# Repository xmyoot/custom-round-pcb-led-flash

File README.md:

# Round LED Flash — Annular Ring Camera Strobe

An advanced, hardware-interlocked **annular ring LED camera flash and video light** engineered in **KiCad 10.0.7**. Designed to fit concentric around photographic lens barrels (84.0 mm OD × 55.0 mm ID), the board integrates a **supercapacitor-buffered boost powertrain**, dual regulated current sinks for a tunable white COB, hardware-enforced timing and safety interlocks, and Bluetooth Low Energy (BLE 5.0) control via an **ESP32-C3**.

---

## 1. System Architecture & Powertrain

```mermaid
flowchart TD
    subgraph PowerInput [Power & Battery Management]
        USB["USB Type-C Receptacle (J1)<br/>GCT USB4085"] --> TUSB["Source Qualification<br/>TI TUSB320LAI (1.5A/3A)"]
        TUSB --> TP4056["300mA Li-ion Charger<br/>TopPower TP4056"]
        BATT["18650 Li-ion Cell<br/>(Rear Holder via J2)"] <--> DW01["Protection Circuit<br/>DW01A + 2x AO3400A"]
        TP4056 --> DW01
        DW01 --> BUCKBOOST["Logic Power Supply<br/>TI TPS63070 Buck-Boost (3.3V)"]
    end

    subgraph Controller [Compute & Connectivity]
        BUCKBOOST --> MCU["ESP32-C3-WROOM-02-N4<br/>BLE 5.0 + UART Fixture"]
        SHUTTER["Shutter Button & Switch"] --> MCU
    end

    subgraph EnergyStorage [Supercapacitor Subsystem]
        DW01 --> LTC3225["Balanced 60mA Charger<br/>Analog Devices LTC3225"]
        LTC3225 --> SCAP["Supercapacitor Bank<br/>2x Eaton 5.0F 2.7V (2.5F @ 4.8V)"]
        SCAP --> BLEED["Dual Discharge Circuit<br/>Active Q34 + Passive R74"]
    end

    subgraph FlashDriver [High-Voltage Flash Powertrain]
        SCAP --> FUSE["4A Fast Fuse (F2)"]
        FUSE --> BOOST["Synchronous Boost Converter<br/>MPS MP3435 (21.07V Out)"]
        BOOST --> CUTOFF["High-Side Safety Cutoff<br/>A&O AO4407A P-MOSFET"]
        CUTOFF --> COB["Tunable White COB LED<br/>Bridgelux Vesta 2700K/6500K"]
        COB --> SINKS["Dual Current Sinks<br/>2x onsemi CAT4101 (200mA/ch)"]
    end

    subgraph SafetyGate [Hardware Safety & Interlocks]
        TIMERS["Dual Hardware Timers<br/>2x LTC6993-1 TimerBlocks"]
        SUPERVISOR["Battery UVLO & Rail Monitors<br/>TI TLV3011 Comparators"]
        SUPERVISOR --> TIMERS
        MCU --> TIMERS
        TIMERS --> CUTOFF
        TIMERS --> SINKS
    end
```

---

## 2. Technical Specifications

| Parameter | Specification | Notes |
| :--- | :--- | :--- |
| **Dimensions** | 84.0 mm OD × 55.0 mm ID annular ring | 14.5 mm radial circuit corridor, 4 layers, 1.6 mm FR-4 |
| **Microcontroller** | Espressif ESP32-C3-WROOM-02-N4 | 32-bit RISC-V @ 160 MHz, BLE 5.0, 4 MB Flash |
| **Battery Interface** | 1S Li-ion 18650 via JST-PH 2.0 mm | Keyed connector, rear holder mount, DW01A protection |
| **System Logic Rail** | 3.3 V regulated @ 500 mA | TI TPS63070 synchronous buck-boost (continuous 2.7 V to 4.35 V) |
| **Energy Buffer** | 2.5 F effective (2× 5.0 F / 2.7 V Eaton HV1020) | Series configuration; 28.8 J total stored energy @ 4.8 V |
| **Capacitor Charger** | ADI LTC3225 active cell balancer | 60 mA constant-current charging from battery |
| **Flash Boost Converter** | MPS MP3435GL-Z synchronous boost | 4.8 V nominal input to 21.07 V output; 10 mΩ current sense (`R270`) |
| **Current Regulation** | Dual onsemi CAT4101 constant-current sinks | 200 mA nominal per channel (warm / cool independent channels) |
| **Optical Emitter** | Bridgelux Vesta Tunable COB (BXRV-TR-2765G) | Off-board emitter in central aperture on dedicated heat spreader |
| **Pulse Duration** | 500 µs to 1000 µs commanded | Firmware pulses gated inside hardware limit window |
| **Hardware Flash Window**| 1.403 ms nominal (1.449 ms max) non-retriggerable | ADI LTC6993-1 hardware timer prevents stuck-on conditions |
| **Hardware Cooldown** | 1.258 s nominal minimum interval | ADI LTC6993-1 timer locks out re-triggering until safe |
| **Service Discharge** | Active dump FET (`Q34`) + permanent passive bleed (`R74`)| Discharges capacitor bank below 0.5 V in <50 minutes |
| **Sensors & Telemetry** | 2× 10 kΩ NTC thermistors (B=3988 K) | Onboard sensor near inner ring; external cell pack NTC (`J3`) |

---

## 3. Design Verification & Analysis

The design has been verified across multiple automated physical and electrical model passes:

- **Schematic Rules (ERC):** 0 errors, 0 warnings ([analysis/draft_erc.rpt](analysis/draft_erc.rpt)).
- **Schematic-to-Layout Parity:** 0 missing nets, 0 footprint mismatches across all 237 placed PCB footprints ([analysis/core_parity_drc.rpt](analysis/core_parity_drc.rpt)).
- **Design Envelope Physics Models:** All 13 hardware corner calculations pass in [scripts/check_design_envelope.py](scripts/check_design_envelope.py):
  - Cap bleed-down time modeled: ~49.5 min to <0.5 V
  - Unpowered ADC pin leakage modeled: 0.111 V max (<0.3 V limit)
  - Loaded input voltage droop: 3.18 V min (exceeds 3.0 V converter threshold)
  - Peak capacitor pulse draw: 3.88 A (well below 4.46 A limit)
  - Hardware window: 1.403 ms (under 2.0 ms safety ceiling)
  - Hardware cooldown: 1.217 s min (exceeds 1.0 s thermal protection threshold)
  - Dual-threshold cell NTC comparator window (0°C to 45°C) fully inhibits charge outside safety envelope
- **Design Review Document:** Full findings triage and analysis matrix documented in [docs/DESIGN_REVIEW.md](docs/DESIGN_REVIEW.md).

---

## 4. Repository Structure

```
custom-round-pcb-led-flash/
├── Round_LED_Flash.kicad_pro    # KiCad 10 project file
├── Round_LED_Flash.kicad_sch    # Master schematic
├── Round_LED_Flash.kicad_pcb    # 4-layer circular PCB layout
├── Round_LED_Flash.kicad_dru    # Project design rules
├── bom/
│   └── bom.csv                  # Enriched BOM with 100% MPN coverage
├── docs/
│   ├── DESIGN_REVIEW.md         # Comprehensive engineering review & triage
│   ├── SYSTEM_ARCHITECTURE.md   # Architectural design baseline & requirements
│   ├── IMPLEMENTATION_STATUS.md # Implementation state & engineering decisions
│   └── BRING_UP_AND_QUALIFICATION.md # Prototype test procedures
├── output/
│   └── pdf/
│       └── Round_LED_Flash_Schematic.pdf # Vector schematic drawing
├── scripts/
│   ├── check_design_envelope.py # 13-point mathematical boundary validation
│   └── select_bom.py            # BOM property assignment and enrichment
└── libraries/                   # Project-specific symbol & footprint libraries
```

---

## 5. Prototype Status & Next Steps

This project is released as a **Rev A Prototype Design Candidate**. All schematics, BOM parts, component footprints, and hardware safety mechanisms are fully scoped and verified against manufacturer specifications. 

Physical assembly and bench bring-up tests (startup rail sweeps, capacitor ESR droop under load, optical pulse duration measurements, and near-field EMC scans) are detailed in [docs/BRING_UP_AND_QUALIFICATION.md](docs/BRING_UP_AND_QUALIFICATION.md).

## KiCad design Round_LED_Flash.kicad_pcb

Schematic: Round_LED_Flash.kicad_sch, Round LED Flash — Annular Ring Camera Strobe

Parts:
C1, C4, C5, C9, C10, C21, C23, C24, C40, C41, C80, C140, C141, C142, C143, C144, C145, C146, C147, C148, C149, C150, C151, C152, C153, C155, C156, C162, C163, C236, C273: 100n; C_0603_1608Metric; MPN GRM188R71H104KA93D
C2: 1u 50V; C_0805_2012Metric; MPN GRM21BR71H105KA12L
C3, C230, C231: 1u 10V; C_0603_1608Metric; MPN GRM188R61C105KA12D
C6: 4.7u 16V; C_0805_2012Metric; MPN GRM21BR71E475KA73L
C7, C274, C283: 100n 50V; C_0603_1608Metric; MPN GRM188R71H104KA93D
C8, C11, C12, C13: 10u 10V; C_0805_2012Metric; MPN GRM21BR61C106KE15L
C14, C15, C16: 22u 16V; C_0805_2012Metric; MPN GRM21BR61C226ME44L
C20: 1u; C_0603_1608Metric; MPN GRM188R61C105KA12D
C22: 10u; C_0805_2012Metric; MPN GRM21BR61C106KE15L
C30, C32: 5F 2.7V; CP_Radial_D10.0mm_P5.00mm; MPN HV1020-2R7505-R
C60: 4.7u 10V; C_0805_2012Metric; MPN GRM21BR71E475KA73L
C61: 2.2u 16V; C_0805_2012Metric; MPN GRM21BR71C225KA12L
C270, C271, C272: 22u 10V; C_1206_3216Metric; MPN GRM31CR61C226KE15L
C275: 2.2u 10V; C_0805_2012Metric; MPN GRM21BR71C225KA12L
C276: 10n; C_0603_1608Metric; MPN GRM188R71H103KA01D
C277: 33n; C_0603_1608Metric; MPN GRM188R71H333KA61D
C278: 47p; C_0603_1608Metric; MPN GRM1885C1H470JA01D
C280, C281, C282: 10u 50V; C_1210_3225Metric; MPN GRM32ER71H106KA12L
C284: 120u 35V; CP_Elec_10x12.6; MPN 35SVPF120M
D1: RED; LED_0603_1608Metric; MPN LTST-C190KRKT
D2: AMBER BLE; LED_0603_1608Metric; MPN LTST-C190KFKT
D3: GREEN; LED_0603_1608Metric; MPN LTST-C190KGKT
D4, D5: PESD5V0S1BA; D_SOD-323; MPN PESD5V0S1BA,115
D6: SMF4L6.0A; D_SOD-123F; MPN SMF4L6.0A
D60: 10V ZENER; D_SOD-123; MPN BZT52C10-7-F
D70: GATE CLAMP; D_SOD-123; MPN BAV21W-7-F
F1: 2A FAST; Fuse_Littelfuse-NANO2-451_453; MPN 0451002.MRL
F2: 7A FAST; Fuse_Littelfuse-NANO2-451_453; MPN 0451007.MRL
H1, H2, H3: M2.5 NPTH; MountingHole_2.7mm_M2.5
J1: USB4085-GF-A; USB_C_Receptacle_GCT_USB4085; MPN USB4085-GF-A
J2: BATTERY; JST_PH_B2B-PH-K_1x02_P2.00mm_Vertical; MPN B2B-PH-K-S(LF)(SN)
J3: BM02B-GHS-TBT(LF)(SN); JST_GH_BM02B-GHS-TBT_1x02-1MP_P1.25mm_Vertical; MPN BM02B-GHS-TBT(LF)(SN)
J4: WARM COB; SolderWire-0.5sqmm_1x02_P4.6mm_D0.9mm_OD2.1mm
J5: COOL COB; SolderWire-0.5sqmm_1x02_P4.6mm_D0.9mm_OD2.1mm
L1: 1.5uH; Coilcraft_XFL4020; MPN XFL4020-152MEC
L2: 1.5uH; L_Coilcraft_XAL7030-152; MPN XAL7030-152MEC
LED1: BXRV-TR-2765G-10A0-A-23; MPN BXRV-TR-2765G-10A0-A-23
Q1, Q2, Q34: AO3400A; SOT-23; MPN AO3400A
Q3, Q22, Q23, Q31, Q32, Q33, Q35, Q61, Q62: MMBT3904-7-F; SOT-23; MPN MMBT3904-7-F
Q20, Q21, Q30: AO3401A; SOT-23; MPN AO3401A
Q60: AO4407A; SOIC-8_3.9x4.9mm_P1.27mm; MPN AO4407A
Q70: SiR800DP-T1-GE3; PowerPAK_SO-8_Single; MPN SiR800DP-T1-GE3
R1: 100; R_0603_1608Metric; MPN RC0603FR-07100RL
R2, R42, R43, R273: 1k; R_0603_1608Metric; MPN RC0603FR-071KL
R3, R68, R69: 47k; R_0603_1608Metric; MPN RC0603FR-0747KL
R4: 887k; R_0603_1608Metric; MPN RC0603FR-07887KL
R5, R7, R18, R20, R21, R22, R23, R40, R41, R62, R63, R162, R163, R236, R237, R242: 10k; R_0603_1608Metric; MPN RC0603FR-0710KL
R6, R11: 150k; R_0603_1608Metric; MPN RC0603FR-07150KL
R8, R13, R50, R51, R52, R53, R60, R64, R65, R66, R67, R70, R71, R83, R84, R152, R220, R221, R235, R274: 100k; R_0603_1608Metric; MPN RC0603FR-07100KL
R9: 4.02k; R_0603_1608Metric; MPN RC0603FR-074K02L
R10: 470k; R_0603_1608Metric; MPN RC0603FR-07470KL
R12, R24, R25, R26, R100, R101, R232: 4.7k; R_0603_1608Metric; MPN RC0603FR-074K7L
R14, R81, R82, R165: 1M; R_0603_1608Metric; MPN RC0603FR-071ML
R15, R233, R234: 2.2k; R_0603_1608Metric; MPN RC0603FR-072K2L
R16, R17: 22; R_0603_1608Metric; MPN RC0603FR-0722RL
R27, R28, R29, R30: 22k; R_0603_1608Metric; MPN RC0603FR-0722KL
R61: 24k; R_0603_1608Metric; MPN RC0603FR-0724KL
R72, R73: 100 0.5W; R_2010_5025Metric; MPN RC2010FK-07100RL
R74: 330 0.25W; R_1206_3216Metric; MPN RC1206FR-07330RL
R80: 6.49k; R_0603_1608Metric; MPN RC0603FR-076K49L
R142: 165k; R_0603_1608Metric; MPN RC0603FR-07165KL
R143: 147k; R_0603_1608Metric; MPN TNPW0603147KBEEA
R153, R272: 10k; R_0603_1608Metric; MPN TNPW060310K0BEEA
R164: 2.21M; R_0603_1608Metric; MPN RC0603FR-072M21L
R200: 137k; R_0603_1608Metric; MPN RC0603FR-07137KL
R201: 240k; R_0603_1608Metric; MPN RC0603FR-07240KL
R210: 357k; R_0603_1608Metric; MPN RC0603FR-07357KL
R211: 146k; R_0603_1608Metric; MPN RC0603FR-07146KL
R230, R231: 2.49k; R_0603_1608Metric; MPN RC0603FR-072K49L
R238: 56k; R_0603_1608Metric; MPN RC0603FR-0756KL
R239: 261k; R_0603_1608Metric; MPN TNPW0603261KBEEA
R240: 100k; R_0603_1608Metric; MPN TNPW0603100KBEEA
R241: 10M; R_0603_1608Metric; MPN RC0603FR-0710ML
R270: 0.010 0.5W; R_0805_2012Metric; MPN WSLP0805R0100FEA
R271: 162k; R_0603_1608Metric; MPN TNPW0603162KBEEA
R275: 120k; R_0603_1608Metric; MPN RC0603FR-07120KL
R276: 22k 0.125W; R_0805_2012Metric; MPN RC0805FR-0722KL
SW1: POWER; SW_SPDT_CK_JS102011SAQN; MPN JS102011SAQN
SW2: SHUTTER; SW_SPST_TL3342; MPN TL3342F160QG
TH1: 10k NTC; R_0603_1608Metric; MPN NTCG163JF103FT1
TH2: 10k CELL NTC; MPN B57861S0103F040
TP1: GND; TestPoint_Pad_D1.5mm
TP2: 3V3; TestPoint_Pad_D1.5mm
TP3: UART_TX_EXT; TestPoint_Pad_D1.5mm
TP4: UART_RX_EXT; TestPoint_Pad_D1.5mm
TP5: MCU_EN; TestPoint_Pad_D1.5mm
TP6: BOOT_N; TestPoint_Pad_D1.5mm
TP7: CAP_BANK; TestPoint_Pad_D1.5mm
TP8: CAP_MID; TestPoint_Pad_D1.5mm
U1: DW01A; SOT-23-6; MPN DW01A
U2: TLV76033DBZR; SOT-23; MPN TLV76033DBZR
U3: TUSB320LAIRWBR; Texas_X2QFN-12_1.6x1.6mm_P0.4mm; MPN TUSB320LAIRWBR
U4, U45: SN74LVC1G04DBVR; SOT-23-5; MPN SN74LVC1G04DBVR
U5: TPS25200DRVR; WSON-6-1EP_2x2mm_P0.65mm_EP1x1.6mm; MPN TPS25200DRVR
U6: TPS63070RNMR; TPS63070_RNM0015A; MPN TPS63070RNMR
U7: TP4056-42-ESOP8; TP4056_TopPower_ESOP8; MPN TP4056-42-ESOP8
U8, U42, U43, U55: TLV3011BIDBVR; SOT-23-6; MPN TLV3011BIDBVR
U9, U54: TPS3808G33DBVR; SOT-23-6; MPN TPS3808G33DBVR
U10: ESP32-C3-WROOM-02-N4; ESP32-C3-WROOM-02_NoViaInPad; MPN ESP32-C3-WROOM-02-N4
U30: LTC3225EDDB#TRMPBF; DFN-10-1EP_2x3mm_P0.5mm_EP0.64x2.4mm; MPN LTC3225EDDB#TRMPBF
U40, U41: LTC6993CS6-1#TRMPBF; SOT-23-6; MPN LTC6993CS6-1#TRMPBF
U44, U46, U47, U48, U49, U50, U51, U52, U53, U56: SN74LVC1G08DBVR; SOT-23-5; MPN SN74LVC1G08DBVR
U60, U61: CAT4101TV-T75; TO-263-5_TabPin3; MPN CAT4101TV-T75
U62, U63: SN74LVC1G125DBVR; SOT-23-5; MPN SN74LVC1G125DBVR
U70: MP3435GL-Z; MP3435_QFN20_3x4; MPN MP3435GL-Z

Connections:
/3V3: C14.1, C15.1, C16.1, C21.1, C22.1, C140.1, C141.1, C142.1, C143.1, C144.1, C145.1, C146.1, C147.1, C148.1, C149.1, C150.1, C151.1, C152.1, C153.1, C155.1, C156.1, C162.1, C163.1, C230.1, C231.1, C236.1, R10.1, R12.1, R20.1, R21.1, R22.1, R23.1, R40.1, R41.1, R62.1, R162.1, R163.1, R210.1, R211.1, R236.1, R237.1, R242.1, TP2.1 (1_1), U6.7 (VOUT), U6.8 (VOUT), U10.1 (3V3), U40.5 (VDD), U41.5 (VDD), U42.6 (VDD), U43.6 (VDD), U44.5 (VCC), U45.5 (VCC), U46.5 (VCC), U47.5 (VCC), U48.5 (VCC), U49.5 (VCC), U50.5 (VCC), U51.5 (VCC), U52.5 (VCC), U53.5 (VCC), U54.5 (SENSE), U54.6 (VDD), U55.6 (VDD), U56.5 (VCC), U60.2 (VIN), U61.2 (VIN), U62.5 (VDD), U63.5 (VDD)
/ADC_BAT: C23.1, R27.2, R28.1, U10.18 (IO0)
/ADC_CAP: C24.1, R29.2, R30.1, U10.17 (IO1)
/ADC_NTC: C41.1, R41.2, TH1.1, U10.15 (IO3)
/ARM: R26.1, R67.1, U10.5 (IO6), U47.2 (B)
/BAT_PROT: C8.1, C9.1, C11.1, C12.1, C13.1, C60.1, F1.2, Q20.2 (S), Q30.2 (S), R1.1, R18.1, R50.1, R60.1, SW1.1 (A), U6.12 (VIN), U6.13 (VIN), U7.5 (BAT), U9.3 (MR_N), U9.5 (SENSE), U9.6 (VDD), U30.9 (VIN)
/BAT_SENSE_SW: Q20.3 (D), R27.1
/BLE_LED: R42.1, U10.13 (IO18)
/BLE_LED_A: D2.2 (A), R42.2
/BOOST_BST: C274.1, U70.4 (BST)
/BOOST_COMP: C277.1, C278.1, U70.13 (COMP)
/BOOST_COMP_R: C277.2, R275.1
/BOOST_EN: R273.2, R274.1, U70.6 (EN)
/BOOST_FB: R271.2, R272.1, U70.14 (FB)
/BOOST_INPUT: D70.2 (A), L2.1, Q70.1 (S), Q70.2 (S), Q70.3 (S)
/BOOST_INPUT_GATE: D70.1 (K), Q70.4 (G), U70.7 (GATE)
/BOOST_OK: R163.2, R165.1, U43.1 (OUT), U48.2 (B)
/BOOST_OUT: C280.1, C281.1, C282.1, C283.1, C284.1, D60.1 (K), Q60.1 (S), Q60.2 (S), Q60.3 (S), R143.1, R232.1, R271.1, R276.1, U70.1 (OUT), U70.2 (OUT), U70.5 (SOUT)
/BOOST_OUT_HW_REF: U43.4 (IN_MINUS), U43.5 (REF)
/BOOST_OUT_HW_SENSE: R143.2, R153.1, R165.2, U43.3 (IN_PLUS)
/BOOST_REQUEST: R273.1, U47.4 (Y), U48.1 (A)
/BOOST_SENSE: Q70.5 (D_5_6_7_8), R270.2, U70.8 (SENSE)
/BOOST_SS: C276.1, U70.15 (SS)
/BOOST_SW: C274.2, L2.2, U70.9 (SW), U70.20 (SW)
/BOOST_VDD: C275.1, U70.12 (VDD)
/BOOT_N: R21.2, TP6.1 (1_1), U10.8 (IO9)
/CAP_BANK: C30.1, F2.1, Q21.2 (S), R51.1, R70.1, R72.1, R73.1, R74.1, R142.1, R239.1, TP7.1 (1_1), U30.10 (COUT)
/CAP_BANK_HW_REF: U42.4 (IN_MINUS), U42.5 (REF)
/CAP_BANK_HW_SENSE: R142.2, R152.1, R164.2, U42.3 (IN_PLUS)
/CAP_CHG_EN: Q32.3 (C), Q33.3 (C), R63.2, R64.1, U30.4 (SHDN)
/CAP_DUMP_BASE: Q35.1 (B), R71.2
/CAP_DUMP_DRAIN: Q34.3 (D), R72.2, R73.2
/CAP_DUMP_GATE: Q34.1 (G), Q35.3 (C), R70.2
/CAP_EN_FEED: Q30.3 (D), R63.1
/CAP_EN_GATE: Q30.1 (G), Q31.3 (C), R60.2
/CAP_FLY_N: C61.2, U30.2 (C_MINUS)
/CAP_FLY_P: C61.1, U30.1 (C_PLUS)
/CAP_FUSED: C270.1, C271.1, C272.1, C273.1, F2.2, R270.1, U70.11 (IN)
/CAP_MID: C30.2, C32.1, TP8.1 (1_1), U30.3 (CX)
/CAP_OK: R162.2, R164.1, U42.1 (OUT), U46.2 (B)
/CAP_PGOOD: R62.2, U30.5 (PGOOD)
/CAP_PROG: R61.1, U30.7 (PROG)
/CAP_READY: R241.1, R242.2, U55.1 (OUT), U56.1 (A)
/CAP_READY_REF: U55.4 (IN_MINUS), U55.5 (REF)
/CAP_READY_SENSE: R239.2, R240.1, R241.2, U55.3 (IN_PLUS)
/CAP_SENSE_SW: Q21.3 (D), R29.1
/CC1: R16.2, U3.1 (CC1)
/CC1_RAW: D4.2 (A2), J1.A5 (CC1), R16.1
/CC2: R17.2, U3.2 (CC2)
/CC2_RAW: D5.2 (A2), J1.B5 (CC2), R17.1
/CC_ALLOWED: R7.1, U4.4 (Y), U5.4 (EN)
/CC_CURRENT_N: R5.2, U3.7 (OUT1), U4.2 (A)
/CC_VBUS_DET: R4.2, U3.4 (VBUS_DET)
/CELL_CS: R2.2, U1.2 (CS)
/CELL_FET_COMMON: Q1.3 (D), Q2.3 (D)
/CELL_IC_VCC: C1.1, R1.2, U1.5 (VCC)
/CELL_N_RAW: C1.2, J2.2, Q1.2 (S), U1.6 (VSS)
/CELL_OC: Q2.1 (G), U1.3 (OC)
/CELL_OD: Q1.1 (G), U1.1 (OD)
/CELL_P: F1.1, J2.1
/CHARGE_ALLOWED: R7.2, R8.1, U7.8 (CE), U8.1 (OUT)
/CHARGE_PROG: R9.1, U7.2 (PROG)
/CHG_LED_A: D1.2 (A), R15.2
/CHRG_N: D1.1 (K), U7.7 (CHRG_N)
/COOLDOWN: U41.6 (OUT), U45.2 (A)
/COOLDOWN_READY: U45.4 (Y), U56.2 (B)
/C_ISET: R231.1, U61.4 (RSET)
/ENERGY_REARM_OK: U49.2 (B), U56.4 (Y)
/FLASH_TRIGGER: U40.1 (TRIG), U50.4 (Y)
/GND: C2.2, C3.2, C4.2, C5.2, C6.2, C7.2, C8.2, C9.2, C10.2, C11.2, C12.2, C13.2, C14.2, C15.2, C16.2, C20.2, C21.2, C22.2, C23.2, C24.2, C32.2, C40.2, C41.2, C60.2, C80.2, C140.2, C141.2, C142.2, C143.2, C144.2, C145.2, C146.2, C147.2, C148.2, C149.2, C150.2, C151.2, C152.2, C153.2, C155.2, C156.2, C162.2, C163.2, C230.2, C231.2, C236.2, C270.2, C271.2, C272.2, C273.2, C275.2, C276.2, C278.2, C280.2, C281.2, C282.2, C283.2, C284.2, D2.1 (K), D3.1 (K), D4.1 (A1), D5.1 (A1), D6.2 (A2), J1.A1 (GND), J1.A12 (GND), J1.B1 (GND), J1.B12 (GND), J1.SH (SHIELD), J3.2 (GND), J3.MP (MOUNT), Q2.2 (S), Q3.2 (E), Q22.2 (E), Q23.2 (E), Q31.2 (E), Q32.2 (E), Q33.2 (E), Q34.2 (S), Q35.2 (E), Q61.2 (E), Q62.2 (E), R2.1, R6.2, R8.2, R9.2, R11.2, R14.2, R24.2, R25.2, R26.2, R28.2, R30.2, R61.2, R64.2, R65.2, R66.2, R74.2, R82.2, R84.2, R100.2, R101.2, R152.2, R153.2, R200.2, R201.2, R220.2, R221.2, R230.2, R231.2, R235.2, R240.2, R272.2, R274.2, R275.2, R276.2, SW1.3 (C), SW2.2, TH1.2, TH2.2, TP1.1 (1_1), U2.3 (GND), U3.3 (PORT), U3.10 (GND), U3.11 (EN_N), U4.3 (GND), U5.5 (GND), U5.7 (EP), U6.4 (GND), U6.10 (PGND), U6.15 (VSEL), U7.3 (GND), U7.9 (EP), U8.2 (GND), U9.2 (GND), U10.9 (GND), U10.19 (GND), U30.6 (VSEL), U30.8 (GND), U30.11 (EP_GND), U40.2 (GND), U41.2 (GND), U42.2 (GND), U43.2 (GND), U44.3 (GND), U45.3 (GND), U46.3 (GND), U47.3 (GND), U48.3 (GND), U49.3 (GND), U50.3 (GND), U51.3 (GND), U52.3 (GND), U53.3 (GND), U54.2 (GND), U55.2 (GND), U56.3 (GND), U60.3 (GND_TAB), U61.3 (GND_TAB), U62.3 (GND), U63.3 (GND), U70.10 (PGND), U70.16 (AGND), U70.17 (PGND), U70.18 (PGND), U70.19 (PGND)
/HW_OK: U48.4 (Y), U49.1 (A), U51.2 (B)
/HW_WINDOW: R66.1, R68.1, R234.1, U51.4 (Y), U52.2 (B), U53.2 (B)
/LED_ANODES: J4.1, J5.1, LED1.1 (W_PLUS), LED1.3 (C_PLUS), Q60.5 (D), Q60.6 (D), Q60.7 (D), Q60.8 (D)
/LED_C_K: J5.2, LED1.4 (C_MINUS), U61.5 (LED)
/LED_GATE_BASE: Q61.1 (B), R234.2, R235.1
/LED_GATE_PULL: Q61.3 (C), R233.2
/LED_POWER_GATE: D60.2 (A), Q60.4 (G), R232.2, R233.1
/LED_W_K: J4.2, LED1.2 (W_MINUS), U60.5 (LED)
/LOGIC_AUX: C10.1, U6.3 (VAUX)
/LOGIC_FB: R10.2, R11.1, U6.5 (FB)
/LOGIC_L1: L1.1, U6.11 (L1)
/LOGIC_L2: L1.2, U6.9 (L2)
/LOGIC_PG: R12.2, R52.1, R53.1, R71.1, U6.2 (PG), U54.3 (MR_N)
/LOGIC_PS_SYNC: R18.2, U6.1 (PS_SYNC)
/MCU_EN: C20.1, R20.2, TP5.1 (1_1), U10.2 (EN)
/PACK_TEMP: J3.1 (NTC), R80.2, R81.1, TH2.1, U7.1 (TEMP)
/PACK_TEMP_HALF: R81.2, R82.1, U8.3 (IN_PLUS)
/POR_OK: R236.2, R238.1, U44.2 (B), U46.1 (A), U54.1 (RESET_N)
/Q31_BASE: Q31.1 (B), R67.2
/Q32_BASE: Q32.1 (B), R68.2
/Q33_BASE: Q33.1 (B), R69.2
/RAILS_OK: U46.4 (Y), U47.1 (A)
/READY_LED: R43.1, U10.14 (IO19)
/READY_LED_A: D3.2 (A), R43.2
/REQ_C: R25.1, U10.4 (IO5), U53.1 (A)
/REQ_W: R24.1, U10.3 (IO4), U52.1 (A)
/SENSE_BASE_0: Q22.1 (B), R52.2
/SENSE_BASE_1: Q23.1 (B), R53.2
/SENSE_GATE_0: Q20.1 (G), Q22.3 (C), R50.2
/SENSE_GATE_1: Q21.1 (G), Q23.3 (C), R51.2
/SHUTTER_N: C40.1, R40.2, SW2.1, U10.10 (IO10)
/SINK_C_EN: R101.1, U53.4 (Y), U61.1 (EN_PWM)
/SINK_W_EN: R100.1, U52.4 (Y), U60.1 (EN_PWM)
/STRAP8: R23.2, U10.7 (IO8)
/SW_ON: R13.1, SW1.2 (B)
/SYS_EN: Q3.3 (C), R13.2, R14.1, U6.14 (EN), U9.1 (RESET_N)
/TEMP_REF: R83.1, U8.5 (REF)
/TEMP_REF_HALF: R83.2, R84.1, U8.4 (IN_MINUS)
/TIMER_WINDOW: U40.6 (OUT), U41.1 (TRIG), U51.1 (A)
/TRIGGER_ALLOWED: U10.6 (IO7), U49.4 (Y), U50.2 (B)
/TRIG_REQ: R22.2, U10.16 (IO2), U44.1 (A)
/TRIG_SAFE: U44.4 (Y), U50.1 (A)
/U40_DIV: R210.2, R220.1, U40.4 (DIV)
/U40_SET: R200.1, U40.3 (SET)
/U41_DIV: R211.2, R221.1, U41.4 (DIV)
/U41_SET: R201.1, U41.3 (SET)
/UART_ENABLE_BASE: Q62.1 (B), R238.2
/UART_OE_N: Q62.3 (C), R237.2, U62.1 (OE_N), U63.1 (OE_N)
/UART_RX: U10.11 (IO20/RXD), U62.4 (Y)
/UART_RX_EXT: TP4.1 (1_1), U62.2 (A)
/UART_TX: U10.12 (IO21/TXD), U63.2 (A)
/UART_TX_EXT: TP3.1 (1_1), U63.4 (Y)
/USB_3V3: C3.1, C4.1, C5.1, C80.1, R5.1, U2.1 (OUT), U3.12 (VDD), U4.5 (VCC), U8.6 (VDD)
/USB_5V: C6.1, R15.1, R80.1, U5.1 (OUT), U7.4 (VCC)
/USB_ILIM: R6.1, U5.2 (ILIM)
/USB_INHIBIT_BASE: Q3.1 (B), R3.2
/VBUS_RAW: C2.1, C7.1, D6.1 (A1), J1.A4 (VBUS), J1.A9 (VBUS), J1.B4 (VBUS), J1.B9 (VBUS), R3.1, R4.1, R65.1, R69.1, U2.2 (IN), U5.6 (IN)
/W_ISET: R230.1, U60.4 (RSET)

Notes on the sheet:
01 / 3.3 V BUCK-BOOST - 500 mA minimum design target
Draft: exact inductor suffix, capacitor MPNs and loop layout still require verification.
02 / BLE CONTROLLER + UART PROGRAMMING
GPIO2 high for boot, then TRIG_REQ output LOW before ARM. GPIO7 reads TRIGGER_ALLOWED.
03 / 2.5 F EFFECTIVE CAP BANK - regulated 4.8 V
Two series cells; midpoint connects to LTC3225 CX. No bleed balancing resistors.
Nominal stored energy 28.8 J. Fused boost branch, timed output cutoff and default-on discharge.
04 / SHUTTER, INDICATORS, LED-AREA NTC
D1 indicates battery charging; D2 BLE; D3 firmware flash-ready. TH1 senses LED-area temperature.
05 / CONNECTORS + 3.3 V UART POGO ACCESS
07 / ADC POWER-OFF ISOLATION - enabled by regulator PG
TPS63070 PG is low with EN low; dividers discharge through their lower resistors.
08 / 4.8 V SUPERCAP CHARGER + AUTOMATIC BALANCING
Charge enabled by ARM; USB presence or timed flash window forces SHDN low.
09 / CELL FUSE + DW01 LOW-SIDE PROTECTION
Raw negative is isolated from all USB, fixture and enclosure grounds.
10 / TYPE-C SOURCE QUALIFICATION - CHARGING ONLY
Default-current and legacy USB sources do not charge this implementation.
11 / PROTECTED VBUS + 300 mA CELL CHARGER
Charging disables logic and cap recharge in hardware. Ground is protected pack negative.
12 / CELL NTC + SHORTED-SENSOR INHIBIT
Open sensor inhibits through TP4056; short inhibits through U8. Check startup and thresholds.
13 / DEFAULT-ON CAPACITOR SERVICE DISCHARGE
Active dump removes most energy; permanent 330ohm bleed provides final discharge. Measure TP7 before service.
14 / INDEPENDENT RAIL INTERLOCKS
Loaded-rail interlocks: cap ~3.39V rising / 3.15V falling; boost ~19.67V / 19.20V.
15 / NON-RETRIGGERABLE PULSE + COOLDOWN
U40: 1.403ms nominal maximum window; U41: 1.258s lockout from each window start.
16 / HARDWARE FLASH PERMISSION + CHANNEL GATING
17 / PHYSICAL LED POWER CUTOFF - DEFAULT OFF
External COB: BXRV-TR-2765G-10A0-A-23, independent channels, bonded heat spreader.
19 / POWER-ON DELAY + Ioff UART ISOLATION
20 / PRE-FLASH ENERGY QUALIFICATION
Nominal cap-ready ~4.51V rising / 4.43V falling. Pulse sag is handled by U42 UVLO.
18 / 21.07 V BOOST + INPUT DISCONNECT / CURRENT LIMIT
Output reservoir is BEFORE physical cutoff. Never add bulk capacitance on LED_ANODES.

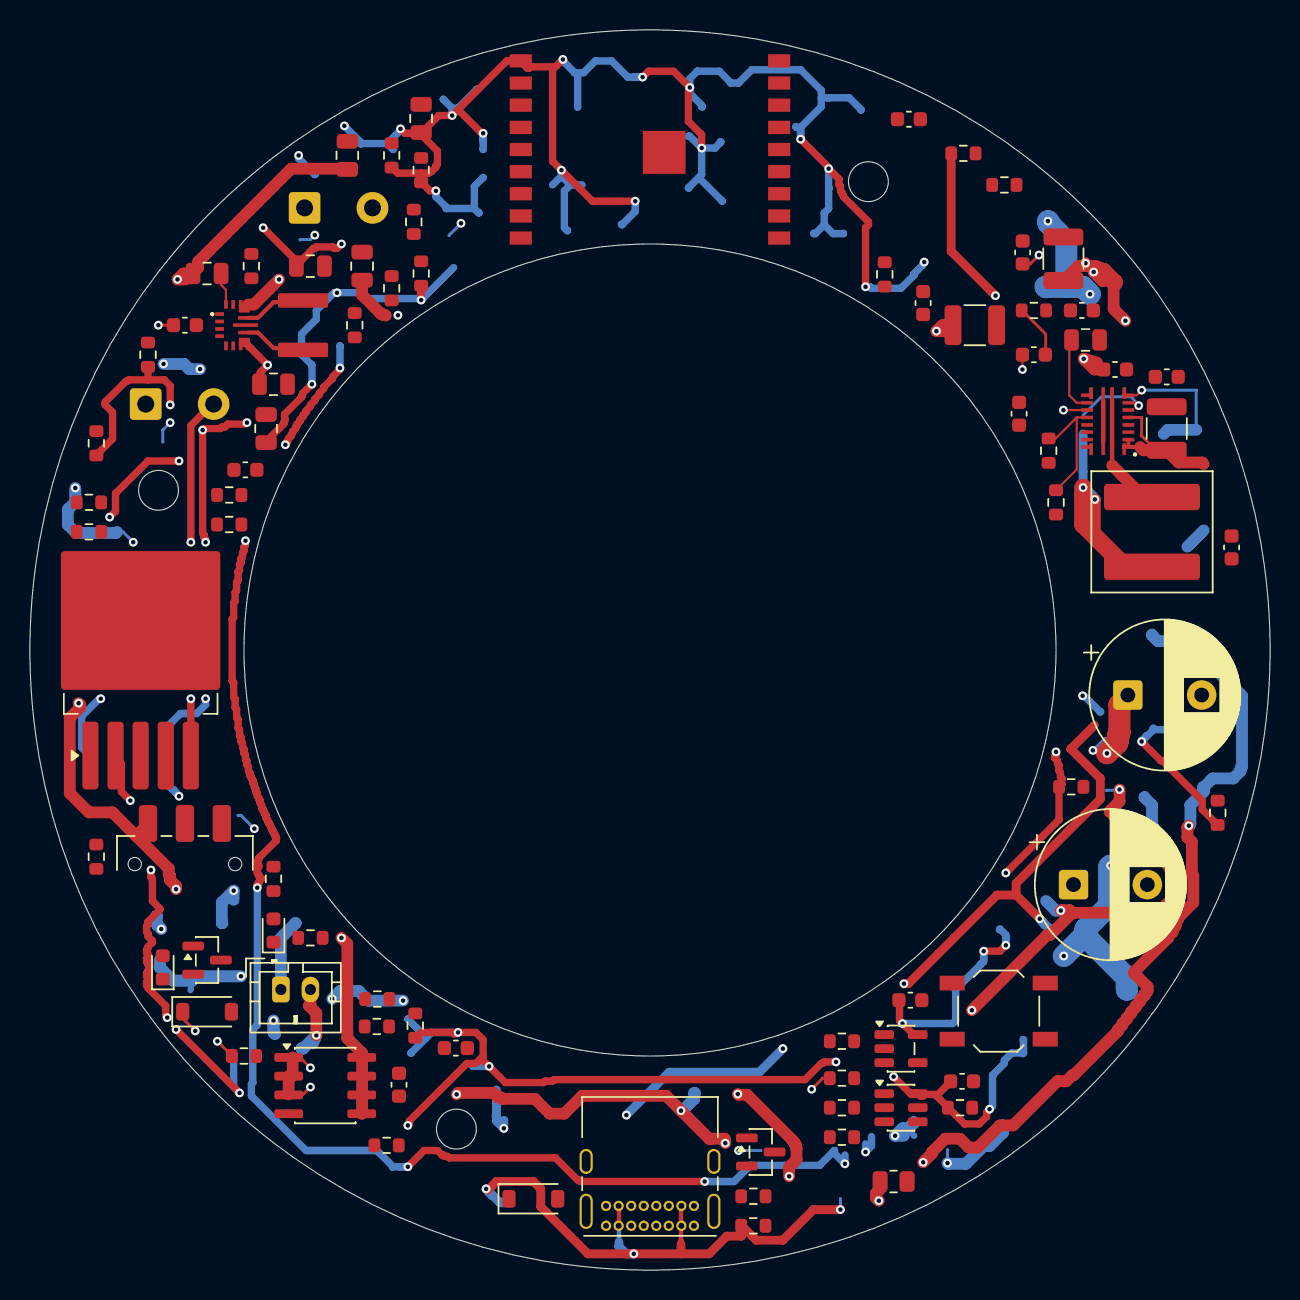
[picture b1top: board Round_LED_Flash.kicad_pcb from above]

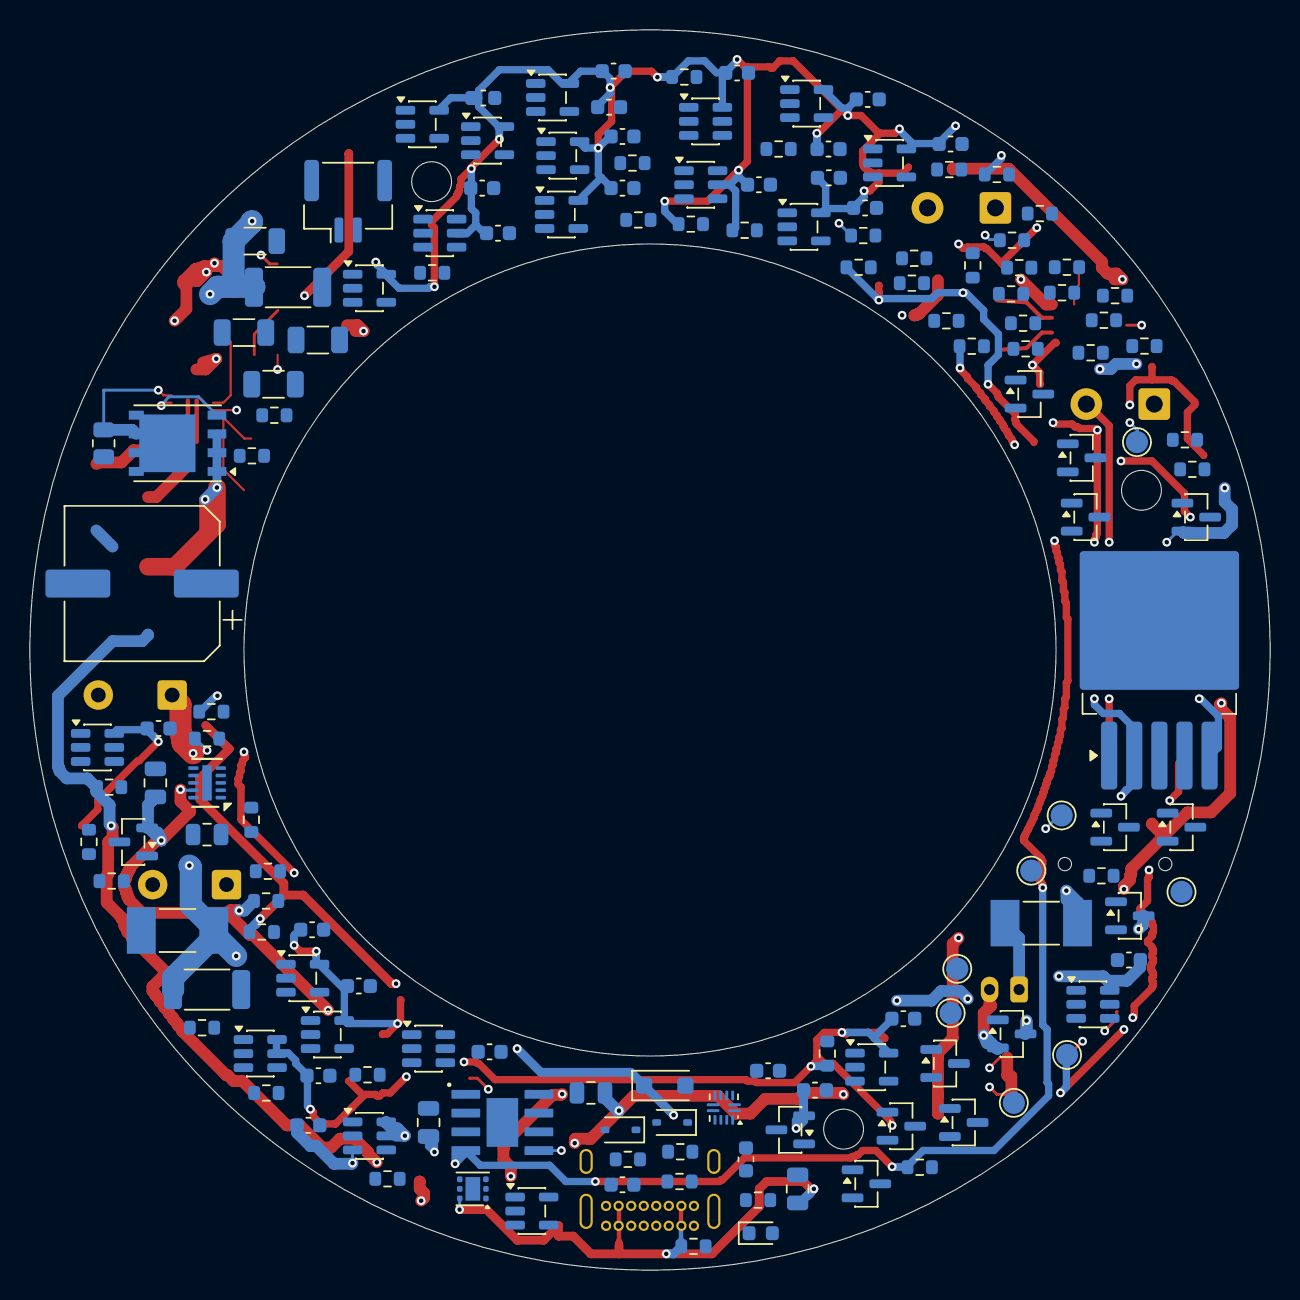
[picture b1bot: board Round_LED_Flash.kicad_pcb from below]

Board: 4 copper layers, 84.0 x 84.0 mm, 237 parts (148 on the bottom side), 128 nets.

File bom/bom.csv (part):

Reference,Qty,Value,Footprint,MPN,Manufacturer,Chosen_Distributor,Datasheet,Validated,DNP,Notes
C2,1,1u 50V,0805,GRM21BR71H105KA12L,Murata,,https://www.murata.com/en-global/api/pdfdownloadapi?cate=luC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,,,Exact nominal/package selection; effective capacitance and source verification pending.
"C3,C230,C231",3,1u 10V,0603,GRM188R61C105KA12D,Murata,,https://www.murata.com/en-global/api/pdfdownloadapi?cate=luC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,,,Exact nominal/package selection; effective capacitance and source verification pending.
C6,1,4.7u 16V,0805,GRM21BR71E475KA73L,Murata,,https://www.murata.com/en-global/api/pdfdownloadapi?cate=luC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,,,Exact nominal/package selection; effective capacitance and source verification pending.
"C7,C274,C283",3,100n 50V,0603,GRM188R71H104KA93D,Murata,,https://www.murata.com/en-global/api/pdfdownloadapi?cate=luC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,,,Exact nominal/package selection; effective capacitance and source verification pending.
"C10,C21,C23,C24,C40,C41,C1,C9,C4,C5,C80,C142,C143,C140,C141,C144,C145,C146,C147,C148,C149,C150,C151,C152,C153,C236,C162,C163,C155,C156,C273",31,100n,0603,GRM188R71H104KA93D,Murata,,https://www.murata.com/en-global/api/pdfdownloadapi?cate=luC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,,,Exact nominal/package selection; effective capacitance and source verification pending.
"C11,C12,C13,C8",4,10u 10V,0805,GRM21BR61C106KE15L,Murata,,https://www.murata.com/en-global/api/pdfdownloadapi?cate=luC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,,,Exact nominal/package selection; effective capacitance and source verification pending.
"C14,C15,C16",3,22u 16V,0805,GRM21BR61C226ME44L,Murata,,https://www.murata.com/en-global/api/pdfdownloadapi?cate=luC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,,,Exact nominal/package selection; effective capacitance and source verification pending.
C20,1,1u,0603,GRM188R61C105KA12D,Murata,,https://www.murata.com/en-global/api/pdfdownloadapi?cate=luC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,,,Exact nominal/package selection; effective capacitance and source verification pending.
C22,1,10u,0805,GRM21BR61C106KE15L,Murata,,https://www.murata.com/en-global/api/pdfdownloadapi?cate=luC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,,,Exact nominal/package selection; effective capacitance and source verification pending.
"C30,C32",2,5F 2.7V,CP_Radial_D10.0mm_P5.00mm,HV1020-2R7505-R,Eaton,,https://www.eaton.com/content/dam/eaton/products/electronic-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,,,Maximum body 10.5 mm diameter x 22.3 mm high. Hand-solder after reflow. Pulse and aged ESR validation pending.
C60,1,4.7u 10V,0805,GRM21BR71E475KA73L,Murata,,https://www.murata.com/en-global/api/pdfdownloadapi?cate=luC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,,,Exact nominal/package selection; effective capacitance and source verification pending.
C61,1,2.2u 16V,0805,GRM21BR71C225KA12L,Murata,,https://www.murata.com/en-global/api/pdfdownloadapi?cate=luC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,,,Exact nominal/package selection; effective capacitance and source verification pending.
"C270,C271,C272",3,22u 10V,1206,GRM31CR61C226KE15L,Murata,,https://www.murata.com/en-global/api/pdfdownloadapi?cate=luC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,,,Exact nominal/package selection; effective capacitance and source verification pending.
C275,1,2.2u 10V,0805,GRM21BR71C225KA12L,Murata,,https://www.murata.com/en-global/api/pdfdownloadapi?cate=luC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,,,Exact nominal/package selection; effective capacitance and source verification pending.
C276,1,10n,0603,GRM188R71H103KA01D,Murata,,https://www.murata.com/en-global/api/pdfdownloadapi?cate=luC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,,,Exact nominal/package selection; effective capacitance and source verification pending.
C277,1,33n,0603,GRM188R71H333KA61D,Murata,,https://www.murata.com/en-global/api/pdfdownloadapi?cate=luC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,,,Exact nominal/package selection; effective capacitance and source verification pending.
C278,1,47p,0603,GRM1885C1H470JA01D,Murata,,https://www.murata.com/en-global/api/pdfdownloadapi?cate=luC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,,,Exact nominal/package selection; effective capacitance and source verification pending.
"C280,C281,C282",3,10u 50V,1210,GRM32ER71H106KA12L,Murata,,https://www.murata.com/en-global/api/pdfdownloadapi?cate=luC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,,,Choose DC-bias-characterized MLCC; total effective ceramic output capacitance >=15uF.
C284,1,120u 35V,CP_Elec_10x12.6,35SVPF120M,Panasonic,,https://industrial.panasonic.com/cdbs/www-data/pdf/AAB8000/A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,,,"Polymer output reservoir; independent package, ESR, ripple and loop-stability verification pending."
D1,1,RED,0603,LTST-C190KRKT,Lite-On,,https://optoelectronics.liteon.com/upload/download/DS-22-99-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,,,Exact LED MPN pending.
D2,1,AMBER BLE,0603,LTST-C190KFKT,Lite-On,,https://optoelectronics.liteon.com/upload/download/DS-22-99-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,,,Select LED MPN and brightness/current before BOM freeze.
D3,1,GREEN,0603,LTST-C190KGKT,Lite-On,,,,,Select LED MPN and brightness/current before BOM freeze.
"D4,D5",2,PESD5V0S1BA,SOD-323,"PESD5V0S1BA,115",Nexperia,,https://assets.nexperia.com/documents/data-sheet/PESD5V0S1BA.pdf,,,"Bidirectional ESD device; comma is part of the orderable MPN, not a second part."
D6,1,SMF4L6.0A,SOD-123F,SMF4L6.0A,Littelfuse,,https://www.littelfuse.com/~/media/electronics/datasheets/tv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,,,6V standoff input transient clamp; place at receptacle. Not protection from a sustained non-compliant supply.
D60,1,10V ZENER,SOD-123,BZT52C10-7-F,Diodes Incorporated,,https://www.diodes.com/datasheet/download/BZT52Cxx.pdf,,,Select 10V zener; cathode to PFET source. Gate transient and off-time verification pending.
D70,1,GATE CLAMP,SOD-123,BAV21W-7-F,Diodes Incorporated,,https://www.diodes.com/datasheet/download/BAV19W-BAV21W.pdf,,,"Low-leakage silicon diode anode at source, cathode at gate; select MPN and check MPS figure4 orientation."
F1,1,2A FAST,Fuse_Littelfuse-NANO2-451_453,0451002.MRL,Littelfuse,,,,,Fuse interruption rating versus actual cell fault current remains a release gate.
F2,1,7A FAST,Fuse_Littelfuse-NANO2-451_453,0451007.MRL,Littelfuse,,,,,Cap bank branch fuse; verify actual capacitor fault current and repetitive pulse I2t.
J1,1,USB4085-GF-A,USB_C_Receptacle_GCT_USB4085,USB4085-GF-A,GCT,,https://gct.co/files/drawings/usb4085.pdf,,,"Charging only. Contacts and shell stakes are through-hole. Local pad clearance is 0.15 mm, per land pattern."
J2,1,BATTERY,JST_PH_B2B-PH-K_1x02_P2.00mm_Vertical,B2B-PH-K-S(LF)(SN),JST,,,,,Raw cell negative is not protected system ground. Fuse and DW01 circuit pending.
J3,1,BM02B-GHS-TBT(LF)(SN),JST_GH_BM02B-GHS-TBT_1x02-1MP_P1.25mm_Vertical,BM02B-GHS-TBT(LF)(SN),JST,,https://www.jst-mfg.com/product/pdf/eng/eGH.pdf,,,Raw cell negative is not protected system ground. Fuse and DW01 circuit pending.
L1,1,1.5uH,Coilcraft_XFL4020,XFL4020-152MEC,Coilcraft,,https://www.coilcraft.com/getmedia/50632d43-da1b-4cdb-8ab4-3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,,,Independent footprint verification remains a release gate.
L2,1,1.5uH,Coilcraft_XAL7030-152,XAL7030-152MEC,Coilcraft,,https://www.coilcraft.com/getmedia/0d05a05e-d55d-4a0c-911d-4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,,,
LED1,1,BXRV-TR-2765G-10A0-A-23,,BXRV-TR-2765G-10A0-A-23,Bridgelux,,https://www.bridgelux.com/sites/default/files/DS350.pdf,,,"OFFBOARD assembly item: 2700/6500K, 15.8mm square, separate warm/cool terminals; mount on electrically isolated heat spreader."
"Q1,Q2,Q34",3,AO3400A,SOT-23,AO3400A,Alpha & Omega Semiconductor,,https://www.aosmd.com/res/data_sheets/AO3400A.pdf,,,
"Q20,Q21,Q30",3,AO3401A,SOT-23,AO3401A,Alpha & Omega Semiconductor,,https://www.aosmd.com/res/data_sheets/AO3401A.pdf,,,Divider high-side switch. Gate pulls to its own source; diode blocks source-to-ADC while off.
"Q22,Q23,Q31,Q32,Q33,Q3,Q35,Q61,Q62",9,MMBT3904-7-F,SOT-23,MMBT3904-7-F,Diodes Incorporated,,https://www.diodes.com/datasheet/download/MMBT3904.pdf,,,Lifecycle/orderable suffix must be rechecked before BOM freeze; -7 listing is NRND.
Q60,1,AO4407A,SOIC-8_3.9x4.9mm_P1.27mm,AO4407A,Alpha & Omega Semiconductor,,https://www.aosmd.com/res/data_sheets/AO4407A.pdf,,,
Q70,1,SiR800DP-T1-GE3,PowerPAK_SO-8_Single,SiR800DP-T1-GE3,Vishay,,https://www.vishay.com/docs/65738/sir800dp.pdf,,,Input disconnect per MPS reference; check linear startup SOA and reverse VGS with D70.
R1,1,100,0603,RC0603FR-07100RL,Yageo,,,,,1% general-purpose resistor; individual sourcing and series-code audit pending.
R4,1,887k,0603,RC0603FR-07887KL,Yageo,,,,,1% general-purpose resistor; individual sourcing and series-code audit pending.
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
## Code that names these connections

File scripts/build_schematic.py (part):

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    # Section 1: logic regulator. Datasheet pin table and adjustable reference.
    ds='https://www.ti.com/lit/ds/symlink/tps63070.pdf'
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    ic('U6','TPS63070',pins,{12:'BAT_PROT',13:'BAT_PROT',14:'SYS_EN',1:'LOGIC_PS_SYNC',15:'GND',6:None,4:'GND',10:'GND',11:'LOGIC_L1',9:'LOGIC_L2',7:'3V3',8:'3V3',5:'LOGIC_FB',3:'LOGIC_AUX',2:'LOGIC_PG'},
       'Round_LED_Flash:TPS63070_RNM0015A',65,65,'TPS63070RNMR','Texas Instruments',ds)
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    r('R10','470k','3V3','LOGIC_FB',115,75)
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    for ref,x in (('C14',115),('C15',165),('C16',215)):
        c(ref,'22u 16V','3V3','GND',x,135,fp='Capacitor_SMD:C_0805_2012Metric')
    r('R12','4.7k','3V3','LOGIC_PG',215,75)
    r('R18','10k','BAT_PROT','LOGIC_PS_SYNC',215,95,notes='Series control isolation required by TPS63070 datasheet section11.1 for pins tied to VIN.')
    add('SW1','POWER','Switch:SW_SPDT','Button_Switch_SMD:SW_SPDT_CK_JS102011SAQN',{1:'BAT_PROT',2:'SW_ON',3:'GND'},65,115,mpn='JS102011SAQN',manufacturer='C&K',notes='Common is pin 2. Position connects enable to cell or ground.')
    r('R13','100k','SW_ON','SYS_EN',65,145)
    r('R14','1M','SYS_EN','GND',165,95)
    # USB pulls enable low with a transistor (added in charging section).
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    r('R30','22k','ADC_CAP','GND',440,145)
    c('C24','100n','ADC_CAP','GND',490,145)
    annotations.append(text('02 / BLE CONTROLLER + UART PROGRAMMING',285,25,2))
    annotations.append(text('GPIO2 high for boot, then TRIG_REQ output LOW before ARM. GPIO7 reads TRIGGER_ALLOWED.',285,165))

    # Section 3: two 5F cells in series, charged/balanced to 4.8V by LTC3225.
    capfp='Capacitor_THT:CP_Radial_D10.0mm_P5.00mm'
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    # Section 8: balanced, limited charge-pump charger. Pin mapping from ADI
    # 3225fb page 5; voltage/current choices from pages 2,3,8. No -1 suffix.
    pins=[('9','VIN','power_in'),('4','SHDN','input'),('6','VSEL','input'),('7','PROG','passive'),('8','GND','power_in'),('11','EP_GND','power_in'),('10','COUT','power_out'),('3','CX','passive'),('1','C_PLUS','passive'),('2','C_MINUS','passive'),('5','PGOOD','open_collector')]
    ic('U30','LTC3225',pins,{9:'BAT_PROT',4:'CAP_CHG_EN',6:'GND',7:'CAP_PROG',8:'GND',11:'GND',10:'CAP_BANK',3:'CAP_MID',1:'CAP_FLY_P',2:'CAP_FLY_N',5:'CAP_PGOOD'},
       'Package_DFN_QFN:DFN-10-1EP_2x3mm_P0.5mm_EP0.64x2.4mm',55,485,
       'LTC3225EDDB#TRMPBF','Analog Devices','https://www.analog.com/media/en/technical-documentation/data-sheets/3225fb.pdf',
       '4.8V selection, automatic cell balancing. EP soldered to ground. Independent package-land check pending.')
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
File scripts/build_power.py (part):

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        datasheet='https://www.littelfuse.com/~/media/electronics/datasheets/tvs_diodes/littelfuse_tvs_diode_smf_datasheet.pdf.pdf',
        notes='6V standoff input transient clamp; place at receptacle. Not protection from a sustained non-compliant supply.')
    pins=[(1,'CC1','bidirectional'),(2,'CC2','bidirectional'),(3,'PORT','input'),(4,'VBUS_DET','input'),(5,'ADDR','input'),(6,'OUT3','open_collector'),(7,'OUT1','open_collector'),(8,'OUT2','open_collector'),(9,'ID','open_collector'),(10,'GND','power_in'),(11,'EN_N','input'),(12,'VDD','power_in')]
    ic('U3','TUSB320LAI',pins,{1:'CC1',2:'CC2',3:'GND',4:'CC_VBUS_DET',5:None,6:None,7:'CC_CURRENT_N',8:None,9:None,10:'GND',11:'GND',12:'USB_3V3'},
       'Package_DFN_QFN:Texas_X2QFN-12_1.6x1.6mm_P0.4mm',825,310,'TUSB320LAIRWBR','Texas Instruments',ti+'tusb320lai.pdf',
       'GPIO UFP mode: OUT1 low only for 1.5A/3A advertisement. Internal Rd; do not fit external Rd.')
    r('R4','887k','VBUS_RAW','CC_VBUS_DET',880,260)
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       {1:None,2:'CC_CURRENT_N',3:'GND',4:'CC_ALLOWED',5:'USB_3V3'},'Package_TO_SOT_SMD:SOT-23-5',930,310,
       'SN74LVC1G04DBVR','Texas Instruments',ti+'sn74lvc1g04.pdf')
    c('C5','100n','USB_3V3','GND',980,310)
    r('R16','22','CC1_RAW','CC1',880,380,notes='Series damping after connector-side TVS; adds 0.43% to nominal 5.1k Rd path.')
    r('R17','22','CC2_RAW','CC2',980,380,notes='Series damping after connector-side TVS; adds 0.43% to nominal 5.1k Rd path.')
    for ref,cc,x in [('D4','CC1_RAW',880),('D5','CC2_RAW',980)]:
        add(ref,'PESD5V0S1BA','Device:D_TVS','Diode_SMD:D_SOD-323',{1:'GND',2:cc},x,355,90,
            mpn='PESD5V0S1BA,115',manufacturer='Nexperia',datasheet='https://assets.nexperia.com/documents/data-sheet/PESD5V0S1BA.pdf',
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
    # Protected VBUS powers the charger. CC and sensor health qualify EN/CE.
    pins=[(1,'OUT','power_out'),(2,'ILIM','passive'),(3,'FAULT_N','open_collector'),(4,'EN','input'),(5,'GND','power_in'),(6,'IN','power_in'),(7,'EP','power_in')]
    ic('U5','TPS25200',pins,{1:'USB_5V',2:'USB_ILIM',3:None,4:'CC_ALLOWED',5:'GND',6:'VBUS_RAW',7:'GND'},
       'Package_SON:WSON-6-1EP_2x2mm_P0.65mm_EP1x1.6mm',335,485,'TPS25200DRVR','Texas Instruments',ti+'tps25200.pdf')
    r('R6','150k','USB_ILIM','GND',390,455)
    r('R7','10k','CC_ALLOWED','CHARGE_ALLOWED',440,455)
    r('R8','100k','CHARGE_ALLOWED','GND',490,455)
    c('C6','4.7u 16V','USB_5V','GND',390,485,fp='Capacitor_SMD:C_0805_2012Metric')
    c('C7','100n 50V','VBUS_RAW','GND',490,485)
    pins=[(1,'TEMP','input'),(2,'PROG','passive'),(3,'GND','power_in'),(4,'VCC','power_in'),(5,'BAT','passive'),(6,'STDBY_N','open_collector'),(7,'CHRG_N','open_collector'),(8,'CE','input'),(9,'EP','power_in')]
    ic('U7','TP4056',pins,{1:'PACK_TEMP',2:'CHARGE_PROG',3:'GND',4:'USB_5V',5:'BAT_PROT',6:None,7:'CHRG_N',8:'CHARGE_ALLOWED',9:'GND'},
       'Round_LED_Flash:TP4056_TopPower_ESOP8',335,550,
       'TP4056-42-ESOP8','NanJing Top Power ASIC','https://www.toppwr.com/uploadfile/file/20230304/640301eae1260.pdf',
       '300mA nominal. Project EP dimensions transcribed from TopPower package drawing page14; independent check remains.')
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
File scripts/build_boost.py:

"""MP3435 energy stage; control-loop and transient qualification remain open."""

def populate(d):
    add,ic,r,c,text,annotations=(d[k] for k in ('add','ic','r','c','text','annotations'))
    ds='https://www.monolithicpower.cn/cn/documentview/productdocument/index/version/2/document_type/Datasheet/lang/en/sku/MP3435GL/'
    pins=[(1,'OUT','passive'),(2,'OUT','passive'),(3,'TM','passive'),(4,'BST','passive'),(5,'SOUT','input'),(6,'EN','input'),(7,'GATE','output'),(8,'SENSE','input'),(9,'SW','passive'),(10,'PGND','power_in'),(11,'IN','power_in'),(12,'VDD','power_out'),(13,'COMP','passive'),(14,'FB','input'),(15,'SS','passive'),(16,'AGND','power_in'),(17,'PGND','power_in'),(18,'PGND','power_in'),(19,'PGND','power_in'),(20,'SW','passive')]
    ic('U70','MP3435',pins,{1:'BOOST_OUT',2:'BOOST_OUT',3:None,4:'BOOST_BST',5:'BOOST_OUT',6:'BOOST_EN',7:'BOOST_INPUT_GATE',8:'BOOST_SENSE',9:'BOOST_SW',10:'GND',11:'CAP_FUSED',12:'BOOST_VDD',13:'BOOST_COMP',14:'BOOST_FB',15:'BOOST_SS',16:'GND',17:'GND',18:'GND',19:'GND',20:'BOOST_SW'},
       'Round_LED_Flash:MP3435_QFN20_3x4',335,860,'MP3435GL-Z','Monolithic Power Systems',ds,
       '21.07V nominal. Kelvin IN/SENSE; compensation must be qualified for actual effective Cout and load steps.')
    add('F2','7A FAST','Device:Fuse','Fuse:Fuse_Littelfuse-NANO2-451_453',{1:'CAP_BANK',2:'CAP_FUSED'},390,835,90,
        mpn='0451007.MRL',manufacturer='Littelfuse',notes='Cap bank branch fuse; verify actual capacitor fault current and repetitive pulse I2t.')
    r('R270','0.010 0.5W','CAP_FUSED','BOOST_SENSE',440,835,fp='Resistor_SMD:R_0805_2012Metric',
      notes='Metal-element 0.5W 1% shunt; maximum steady current-limit dissipation 0.397W before tolerance. Fault pulses are time-limited by converter.')
    # Stock PowerPAK land pattern represents the continuous drain with pad 5.
    pins=[(1,'S','passive'),(2,'S','passive'),(3,'S','passive'),(4,'G','input'),(5,'D_5_6_7_8','passive')]
    ic('Q70','SiR800DP',pins,{1:'BOOST_INPUT',2:'BOOST_INPUT',3:'BOOST_INPUT',4:'BOOST_INPUT_GATE',5:'BOOST_SENSE'},
       'Package_SO:PowerPAK_SO-8_Single',440,885,'SiR800DP-T1-GE3','Vishay','https://www.vishay.com/docs/65738/sir800dp.pdf',
       'Input disconnect per MPS reference; check linear startup SOA and reverse VGS with D70.')
    add('D70','GATE CLAMP','Device:D','Diode_SMD:D_SOD-123',{1:'BOOST_INPUT_GATE',2:'BOOST_INPUT'},490,885,90,
        notes='Low-leakage silicon diode anode at source, cathode at gate; select MPN and check MPS figure4 orientation.')
    add('L2','1.5uH','Device:L','Inductor_SMD:L_Coilcraft_XAL7030-152',{1:'BOOST_INPUT',2:'BOOST_SW'},490,835,90,
        mpn='XAL7030-152MEC',manufacturer='Coilcraft',datasheet='https://www.coilcraft.com/getmedia/0d05a05e-d55d-4a0c-911d-46bd73686633/xal7030.pdf')
    for ref,x,y in [('C270',390,925),('C271',440,925),('C272',490,925)]:
        c(ref,'22u 10V','CAP_FUSED','GND',x,y,fp='Capacitor_SMD:C_1206_3216Metric')
    c('C273','100n','CAP_FUSED','GND',390,950)
    c('C274','100n 50V','BOOST_BST','BOOST_SW',440,950)
    c('C275','2.2u 10V','BOOST_VDD','GND',490,950)
    c('C276','10n','BOOST_SS','GND',390,975)
    r('R271','162k','BOOST_OUT','BOOST_FB',580,835)
    r('R272','10k','BOOST_FB','GND',630,835)
    r('R273','1k','BOOST_REQUEST','BOOST_EN',680,835)
    r('R274','100k','BOOST_EN','GND',730,835)
    # Conservative starting compensation, not copied unmodified from 12V circuit.
    # RHP zero ~84kHz at 3.3V/0.66A/1.5uH; target crossover about 1kHz.
    c('C277','33n','BOOST_COMP','BOOST_COMP_R',580,885)
    r('R275','120k','BOOST_COMP_R','GND',630,885,
      notes='Engineering starting value only. Measure/validate Bode margin and short flash load response before release.')
    c('C278','47p','BOOST_COMP','GND',680,885)
    for ref,x in [('C280',580),('C281',630),('C282',680)]:
        c(ref,'10u 50V','BOOST_OUT','GND',x,930,fp='Capacitor_SMD:C_1210_3225Metric',
          notes='Choose DC-bias-characterized MLCC; total effective ceramic output capacitance >=15uF.')
    c('C283','100n 50V','BOOST_OUT','GND',730,930)
    add('C284','120u 35V','Device:C_Polarized','Capacitor_SMD:CP_Elec_10x12.6',{1:'BOOST_OUT',2:'GND'},730,885,90,
        mpn='35SVPF120M',manufacturer='Panasonic',datasheet='https://industrial.panasonic.com/cdbs/www-data/pdf/AAB8000/AAB8000COL87.pdf',
        notes='Polymer output reservoir; independent package, ESR, ripple and loop-stability verification pending.')
    r('R276','22k 0.125W','BOOST_OUT','GND',580,975,
      notes='Discharges output reservoir; about 10s to 0.5V at 120uF nominal. Not on switched LED rail.')
    annotations.append(text('18 / 21.07 V BOOST + INPUT DISCONNECT / CURRENT LIMIT',285,820,2))
    annotations.append(text('Output reservoir is BEFORE physical cutoff. Never add bulk capacitance on LED_ANODES.',285,1010))

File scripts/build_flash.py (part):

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
    # Series high-side cutoff removes LED energy if a current sink shorts.
    pins=[(1,'S','passive'),(2,'S','passive'),(3,'S','passive'),(4,'G','input'),(5,'D','passive'),(6,'D','passive'),(7,'D','passive'),(8,'D','passive')]
    ic('Q60','AO4407A',pins,{1:'BOOST_OUT',2:'BOOST_OUT',3:'BOOST_OUT',4:'LED_POWER_GATE',5:'LED_ANODES',6:'LED_ANODES',7:'LED_ANODES',8:'LED_ANODES'},
       'Package_SO:SOIC-8_3.9x4.9mm_P1.27mm',55,860,'AO4407A','Alpha & Omega Semiconductor','https://www.aosmd.com/res/data_sheets/AO4407A.pdf')
    r('R232','4.7k','BOOST_OUT','LED_POWER_GATE',110,835)
    r('R233','2.2k','LED_POWER_GATE','LED_GATE_PULL',160,835)
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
